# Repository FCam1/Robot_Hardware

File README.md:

# Robot_Hardware
## Descriptif fichiers :

STM32PAP board : blue pill + 2x drivers PAP  

Master board : Compatible Blue pill et STM32F103ZET6 + MAX485 +74LS241 (pour AX et XM) 

IMU adaptator : Carte a connecter sur l'IMU : [IMU280ZA-209](http://www.aceinna.com/userfiles/files/Datasheets/Inertial-System-Datasheets/6020-2810-01___IMU280ZA_Datasheet.pdf) (équipé du  connecteur CLM-110-02)

CLM-110-02 (.lib): connecteur IMU

[POLOLU 4988](https://www.pololu.com/product/1182) (.lib): driver moteur PAP  

STM32F103ZET6 (.lib): librairie EAGLE. Informations [ICI](http://wiki.stm32duino.com/index.php?title=Vcc-gnd.com_STM32F103ZET6). 

auto fuse (.lib): porte fusible (ref: [PC AUTO FUSE SOCKET](https://www.mouser.fr/ProductDetail/Keystone-Electronics/3522-2/?qs=%2fha2pyFadujcR%252bwSIP7oJU1VF30m3fPHKLRW1u8sLVY%3d))

stm32duino boards (.lib): librairie EAGLE contenant  Black Pill - Blue Pill - Maple Mini from Baite - LeafLab . Source et auteur [ICI](http://www.stm32duino.com/viewtopic.php?f=9&t=782&start=10)

## Instructions chargement bootloader :

Bluepill et stm32f103ZE: Procédure [ici](http://wiki.stm32duino.com/index.php?title=Burning_the_bootloader). Alternative pour Windows [Ici](https://github.com/rogerclarkmelbourne/Arduino_STM32/wiki/Flashing-Bootloader-for-BluePill-Boards)  

[Driver](http://www.st.com/content/st_com/en/products/development-tools/software-development-tools/stm32-software-development-tools/stm32-utilities/stsw-link009.html) pour ST-LINK/V2 sous Windows. 

Binaries : [generic_boot20_pc13.bin](https://github.com/rogerclarkmelbourne/STM32duino-bootloader/tree/master/binaries)  nécessaire pour les Bluepill et stm32f103ZE

## STM32F103ZET6 :

ST Datasheet famille STM32F1 : http://www.st.com/content/ccc/resource/technical/document/reference_manual/59/b9/ba/7f/11/af/43/d5/CD00171190.pdf/files/CD00171190.pdf/jcr:content/translations/en.CD00171190.pdf

ST Datasheet spécifique STM32F103xE : http://www.st.com/resource/en/datasheet/stm32f103ze.pdf  

### Pinouts and pin descriptions (not exhaustive):

5V tolerant : UART1, UART3, UART4, UART5, SPI2, PD8, PD9, PD10, PD11  
Not 5V tolerant : UART2, SPI3, SPI1

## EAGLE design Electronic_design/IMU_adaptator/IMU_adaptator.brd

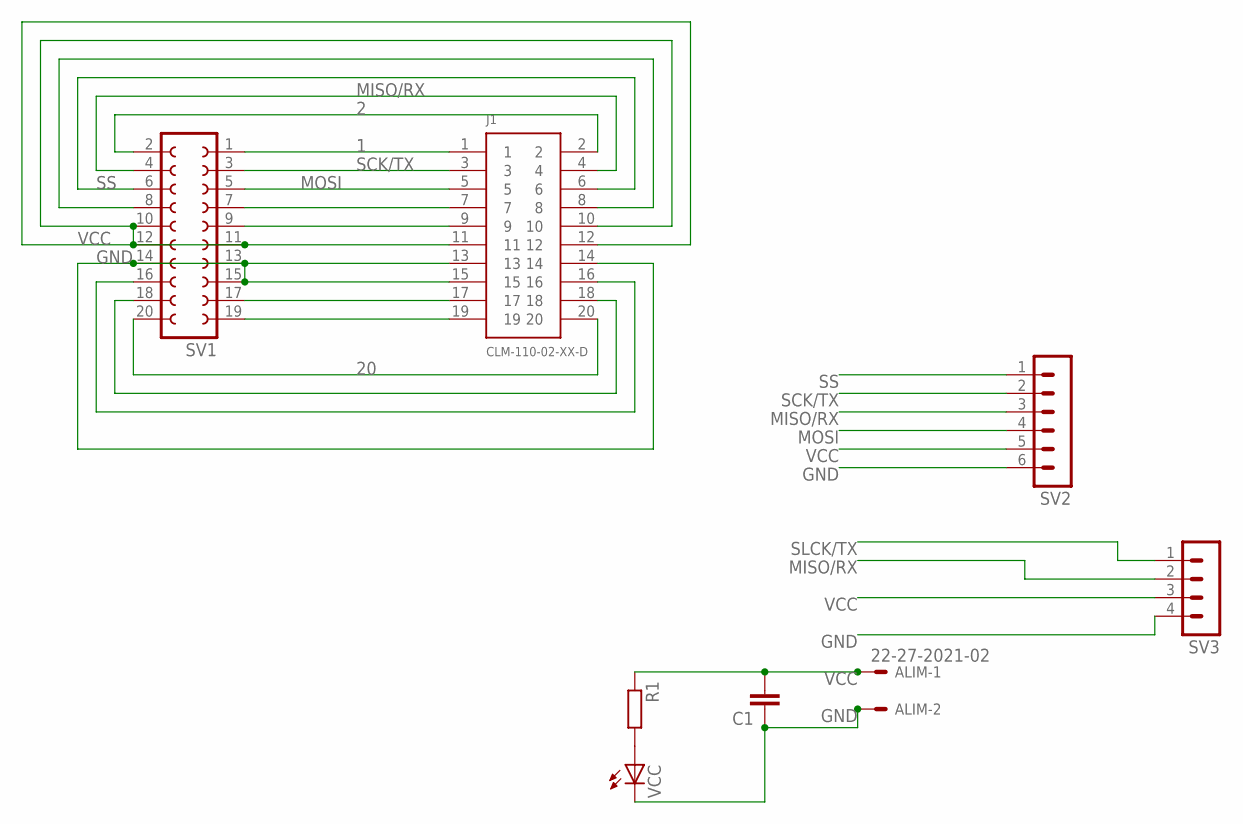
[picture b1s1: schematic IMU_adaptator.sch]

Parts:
ALIM: 22-27-2021-02; 6410-02
C1: C; C0805
J1: CLM-110-02-XX-D
R1: R-EU_0204/5; 0204/5
SV1: FE10-2
SV2: MA06-1
SV3: MA04-1
VCC: LED_ELD260; LED_LD260

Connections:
1: J1.1, SV1.1
2: J1.2, SV1.2
20: J1.20, SV1.20
GND: ALIM.2, C1.1, J1.13, J1.14, J1.15, SV1.13, SV1.14, SV1.15, SV2.6, SV3.4, VCC.K (C)
MISO/RX: J1.4, SV1.4, SV2.3, SV3.2
MOSI: J1.5, SV1.5, SV2.4
unnamed: R1.2, VCC.A
unnamed: J1.7, SV1.7
unnamed: J1.9, SV1.9
unnamed: J1.17, SV1.17
unnamed: J1.19, SV1.19
unnamed: J1.8, SV1.8
unnamed: J1.18, SV1.18
unnamed: J1.16, SV1.16
SCK/TX: J1.3, SV1.3, SV2.2
SLCK/TX: SV3.1
SS: J1.6, SV1.6, SV2.1
VCC: ALIM.1, C1.2, J1.10, J1.11, J1.12, R1.1, SV1.10, SV1.11, SV1.12, SV2.5, SV3.3

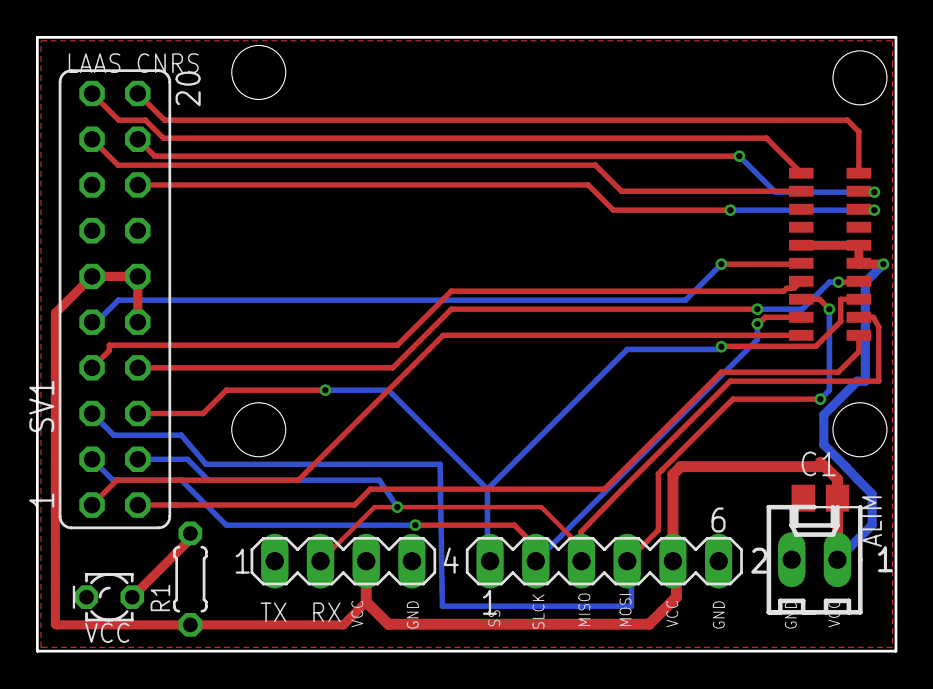
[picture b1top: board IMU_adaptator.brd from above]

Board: 2 copper layers, 47.7 x 34.1 mm, 8 parts (1 on the bottom side), 17 nets.

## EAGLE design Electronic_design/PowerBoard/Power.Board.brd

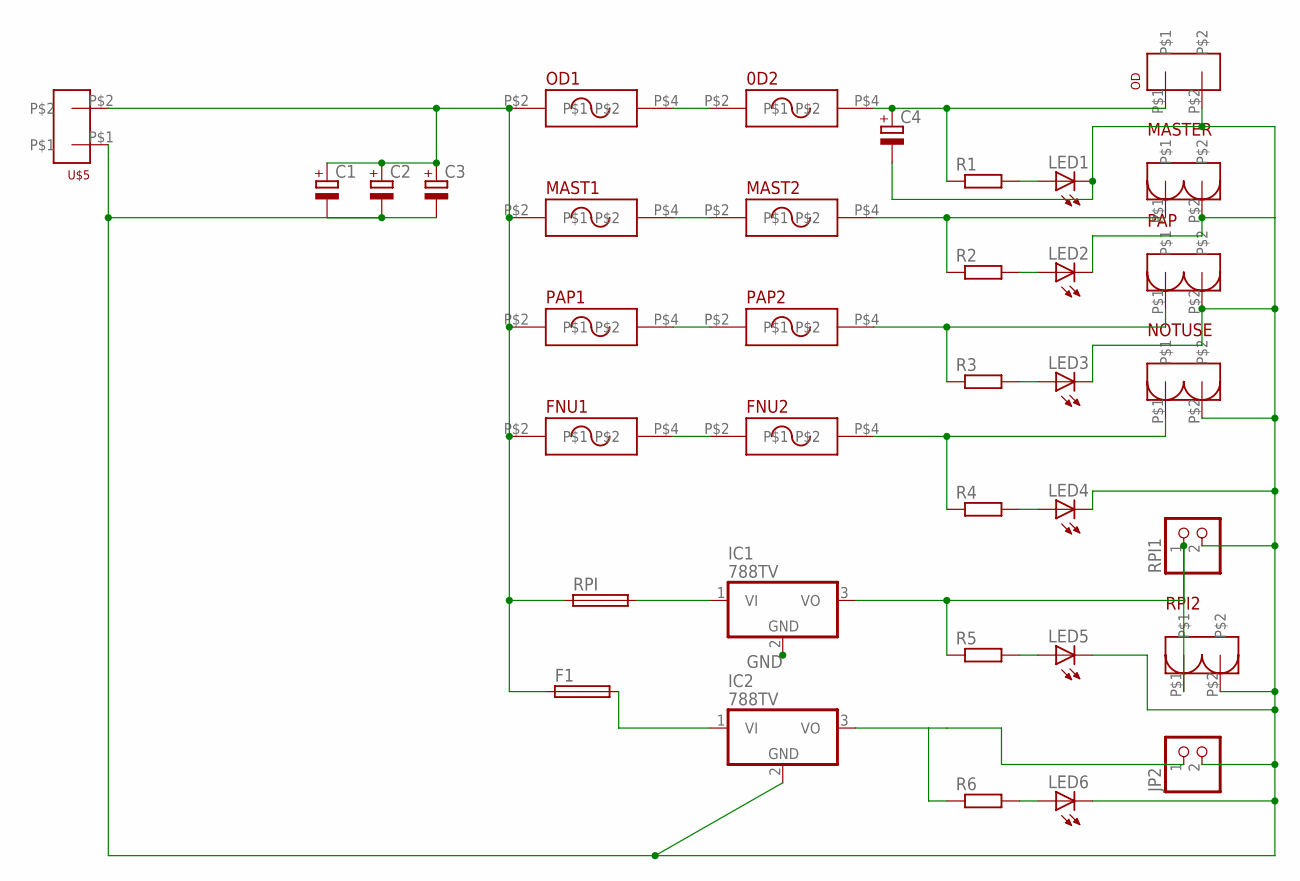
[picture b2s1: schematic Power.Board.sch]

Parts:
0D2: AUTO_FUSE
C1, C2, C3: CPOL-EUE7.5-18; E7,5-18
C4: CPOL-EUE5-13; E5-13
F1: SHK20L
FNU1, FNU2: AUTO_FUSE
IC1, IC2: 788TV; TO220V
JP2: PINHD-1X2; 1X02
LED1, LED2, LED3, LED4, LED5, LED6: LED_ELD260; LED_LD260
MAST1, MAST2: AUTO_FUSE
MASTER: GREEN_HEADER
NOTUSE: GREEN_HEADER
OD: 3MM_HEADER_2
OD1: AUTO_FUSE
PAP: GREEN_HEADER
PAP1, PAP2: AUTO_FUSE
R1, R2, R3, R4, R5, R6: R0207/10; 0207/10
RPI: SHK20L
RPI1: PINHD-1X2; 1X02
RPI2: GREEN_HEADER
U$5: 3MM_HEADER_2

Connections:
12V: C1.+, C2.+, C3.+, F1.1A, FNU1.P$2, MAST1.P$2, OD1.P$2, PAP1.P$2, RPI.1A, U$5.P$2
GND: C1.-, C2.-, C3.-, C4.-, IC1.2 (GND), IC2.2 (GND), JP2.2, LED1.K (C), LED2.K (C), LED3.K (C), LED4.K (C), LED5.K (C), LED6.K (C), MASTER.P$2, NOTUSE.P$2, OD.P$2, PAP.P$2, RPI1.2, RPI2.P$2, U$5.P$1
unnamed: PAP.P$1, PAP2.P$4, R3.1
unnamed: 0D2.P$2, OD1.P$4
unnamed: MAST1.P$4, MAST2.P$2
unnamed: PAP1.P$4, PAP2.P$2
unnamed: IC1.1 (VI), RPI.2A
unnamed: 0D2.P$4, C4.+, OD.P$1, R1.1
unnamed: MAST2.P$4, MASTER.P$1, R2.1
unnamed: IC1.3 (VO), R5.1, RPI1.1, RPI2.P$1
unnamed: IC2.3 (VO), JP2.1, R6.1
unnamed: FNU1.P$4, FNU2.P$2
unnamed: FNU2.P$4, NOTUSE.P$1, R4.1
unnamed: LED1.A, R1.2
unnamed: LED2.A, R2.2
unnamed: LED3.A, R3.2
unnamed: LED4.A, R4.2
unnamed: LED5.A, R5.2
unnamed: LED6.A, R6.2
unnamed: F1.2A, IC2.1 (VI)

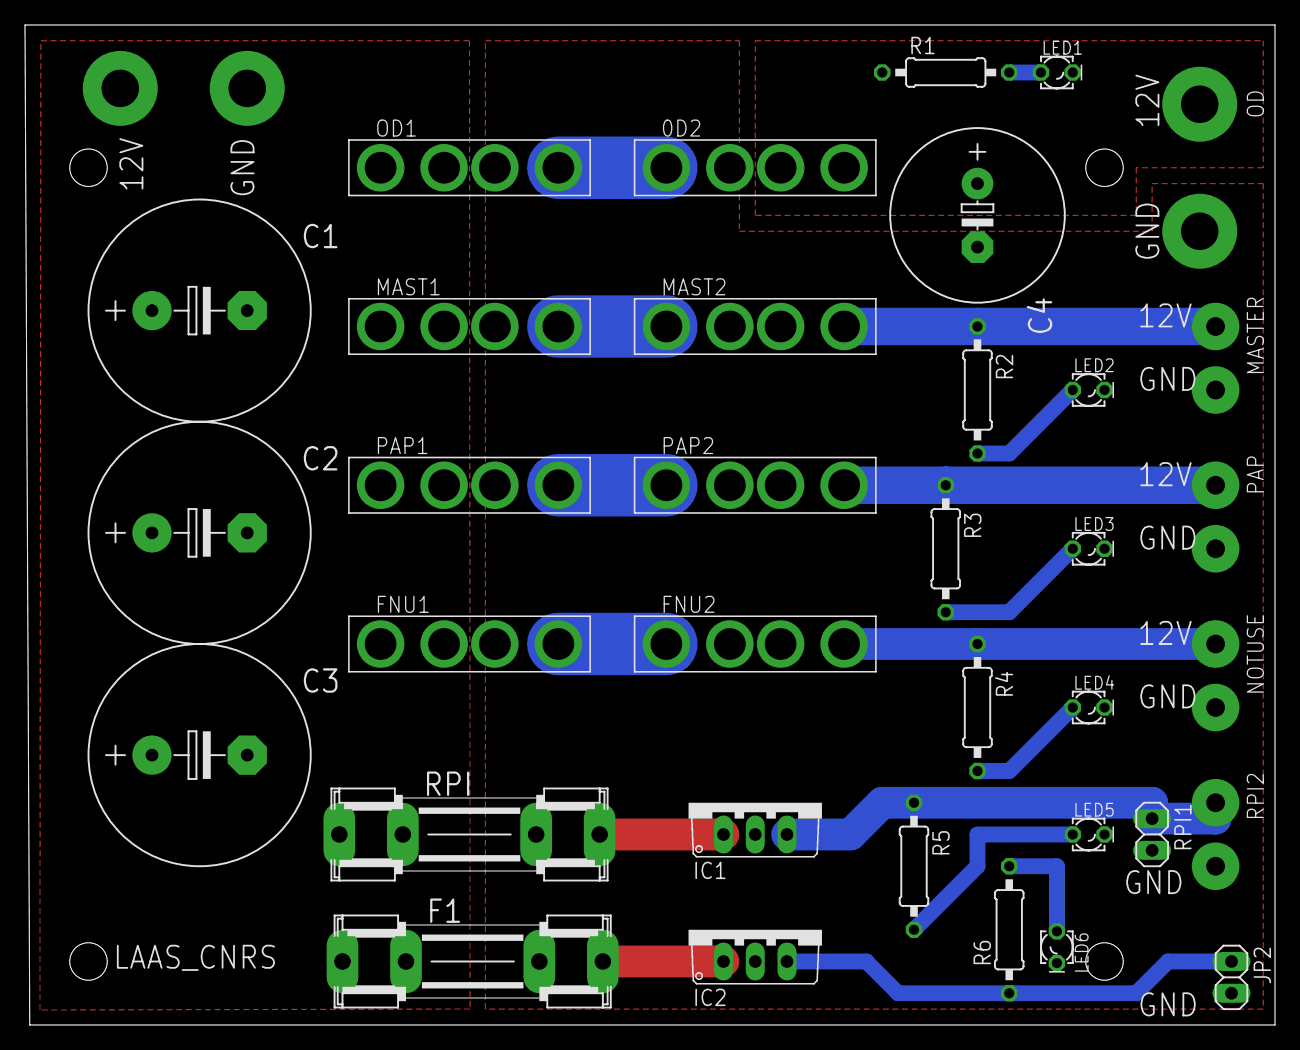
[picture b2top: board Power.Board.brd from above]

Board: 2 copper layers, 100.0 x 80.0 mm, 37 parts (0 on the bottom side), 20 nets.

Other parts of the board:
U$1: TROUS_FIXATION

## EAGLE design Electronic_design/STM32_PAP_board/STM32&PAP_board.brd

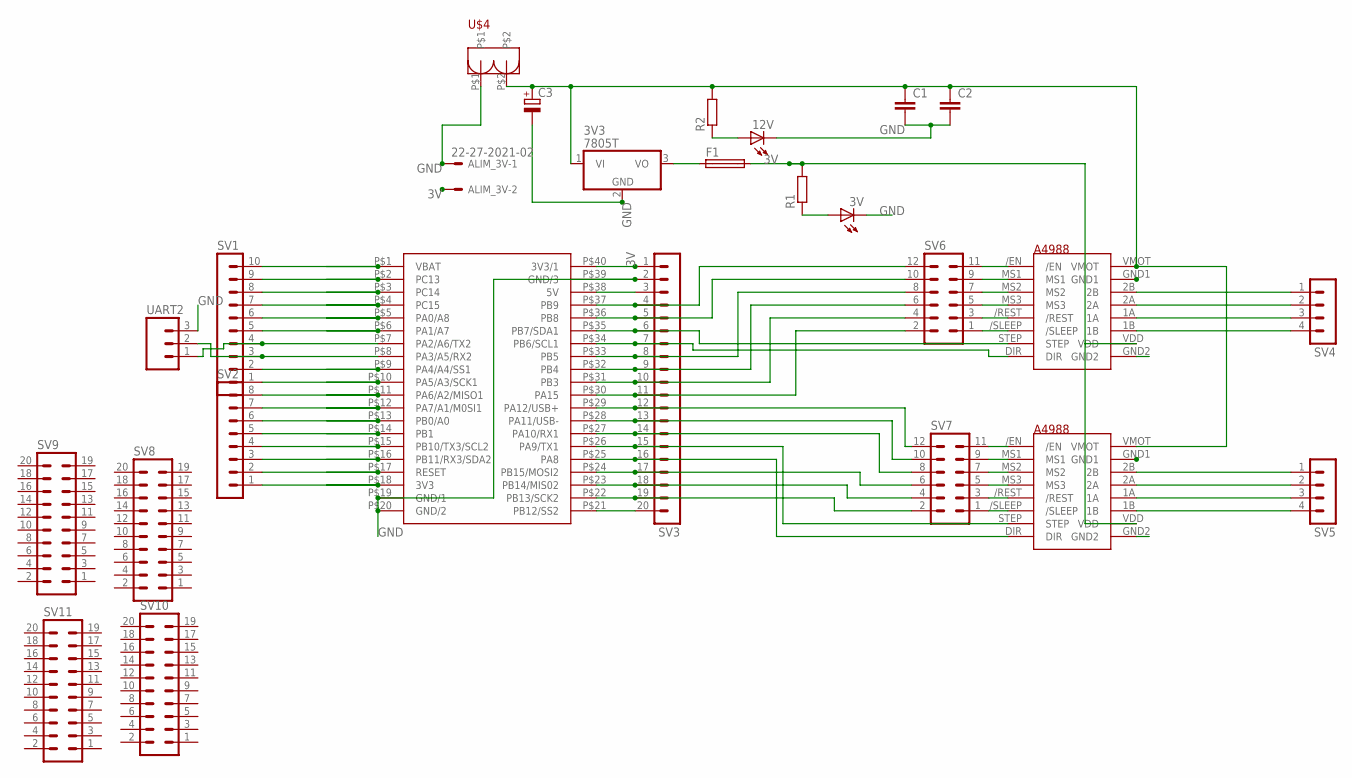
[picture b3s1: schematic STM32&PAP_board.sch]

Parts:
3V, 12V: LED_ELD260; LED_LD260
3V3: 7805T; TO220H
ALIM_3V: 22-27-2021-02; 6410-02
C1, C2: C5/5; C5B5
C3: CPOL-EUE5-13; E5-13
F1: TR5
R1, R2: R0204/7; 0204/7
SV1: MA10-1
SV2: MA08-1
SV3: MA20-1
SV4, SV5: MA04-1
SV6, SV7: MA06-2
SV8, SV9, SV10, SV11: MA10-2
U$1, U$2: POLOLU_A4988_MOTOR_DRIVER
U$3: BLUEPILL
U$4: GREEN_HEADER
UART2: MA03; 03P

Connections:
3V: ALIM_3V.2, F1.2, R1.2, SV3.1, U$1.VDD, U$2.VDD, U$3.P$40 (3V3/1)
GND: 3V.K (C), 3V3.2 (GND), 12V.K (C), ALIM_3V.1, C1.2, C2.2, C3.-, SV3.2, U$3.P$19 (GND/1), U$3.P$20 (GND/2), U$3.P$39 (GND/3), U$4.P$1, UART2.3
unnamed: SV5.1, U$2.2B
unnamed: SV5.2, U$2.2A
unnamed: SV2.1, U$3.P$18 (3V3)
unnamed: SV2.2, U$3.P$17 (RESET)
unnamed: SV2.3, U$3.P$16 (PB11/RX3/SDA2)
unnamed: SV2.4, U$3.P$15 (PB10/TX3/SCL2)
unnamed: SV2.5, U$3.P$14 (PB1)
unnamed: SV2.6, U$3.P$13 (PB0/A0)
unnamed: SV2.7, U$3.P$12 (PA7/A1/M0SI1)
unnamed: SV2.8, U$3.P$11 (PA6/A2/MISO1)
unnamed: SV1.1, U$3.P$10 (PA5/A3/SCK1)
unnamed: SV1.2, U$3.P$9 (PA4/A4/SS1)
unnamed: SV1.3, U$3.P$8 (PA3/A5/RX2), UART2.2
unnamed: SV1.4, U$3.P$7 (PA2/A6/TX2), UART2.1
unnamed: SV1.5, U$3.P$6 (PA1/A7)
unnamed: SV1.6, U$3.P$5 (PA0/A8)
unnamed: SV1.7, U$3.P$4 (PC15)
unnamed: SV1.8, U$3.P$3 (PC14)
unnamed: SV1.9, U$3.P$2 (PC13)
unnamed: SV1.10, U$3.P$1 (VBAT)
unnamed: SV6.1, U$1./SLEEP
unnamed: SV5.3, U$2.1A
unnamed: SV3.3, U$3.P$38 (5V)
unnamed: SV3.4, SV6.12, U$3.P$37 (PB9)
unnamed: SV3.5, SV6.10, U$3.P$36 (PB8)
unnamed: SV3.7, U$1.DIR, U$3.P$34 (PB6/SCL1)
unnamed: SV3.9, SV6.6, U$3.P$32 (PB4)
unnamed: SV3.10, SV6.4, U$3.P$31 (PB3)
unnamed: SV3.11, SV6.2, U$3.P$30 (PA15)
unnamed: SV3.12, SV7.12, U$3.P$29 (PA12/USB+)
unnamed: SV3.13, SV7.10, U$3.P$28 (PA11/USB-)
unnamed: SV3.14, SV7.8, U$3.P$27 (PA10/RX1)
unnamed: SV3.15, U$2.STEP, U$3.P$26 (PA9/TX1)
unnamed: SV3.16, U$2.DIR, U$3.P$25 (PA8)
unnamed: SV3.17, SV7.6, U$3.P$24 (PB15/MOSI2)
unnamed: SV3.18, SV7.4, U$3.P$23 (PB14/MIS02)
unnamed: SV3.19, SV7.2, U$3.P$22 (PB13/SCK2)
unnamed: SV3.20, U$3.P$21 (PB12/SS2)
unnamed: 3V3.3 (VO), F1.1
unnamed: 3V3.1 (VI), C1.1, C2.1, C3.+, R2.2, U$1.VMOT, U$2.VMOT, U$4.P$2
unnamed: 3V.A, R1.1
unnamed: SV5.4, U$2.1B
unnamed: 12V.A, R2.1
unnamed: SV4.1, U$1.2B
unnamed: SV4.2, U$1.2A
unnamed: SV4.3, U$1.1A
unnamed: SV4.4, U$1.1B
unnamed: SV6.3, U$1./REST
unnamed: SV6.5, U$1.MS3
unnamed: SV6.7, U$1.MS2
unnamed: SV6.9, U$1.MS1
unnamed: SV6.11, U$1./EN
unnamed: SV3.6, U$1.STEP, U$3.P$35 (PB7/SDA1)
unnamed: SV3.8, SV6.8, U$3.P$33 (PB5)
unnamed: SV7.11, U$2./EN
unnamed: SV7.9, U$2.MS1
unnamed: SV7.7, U$2.MS2
unnamed: SV7.5, U$2.MS3
unnamed: SV7.3, U$2./REST
unnamed: SV7.1, U$2./SLEEP

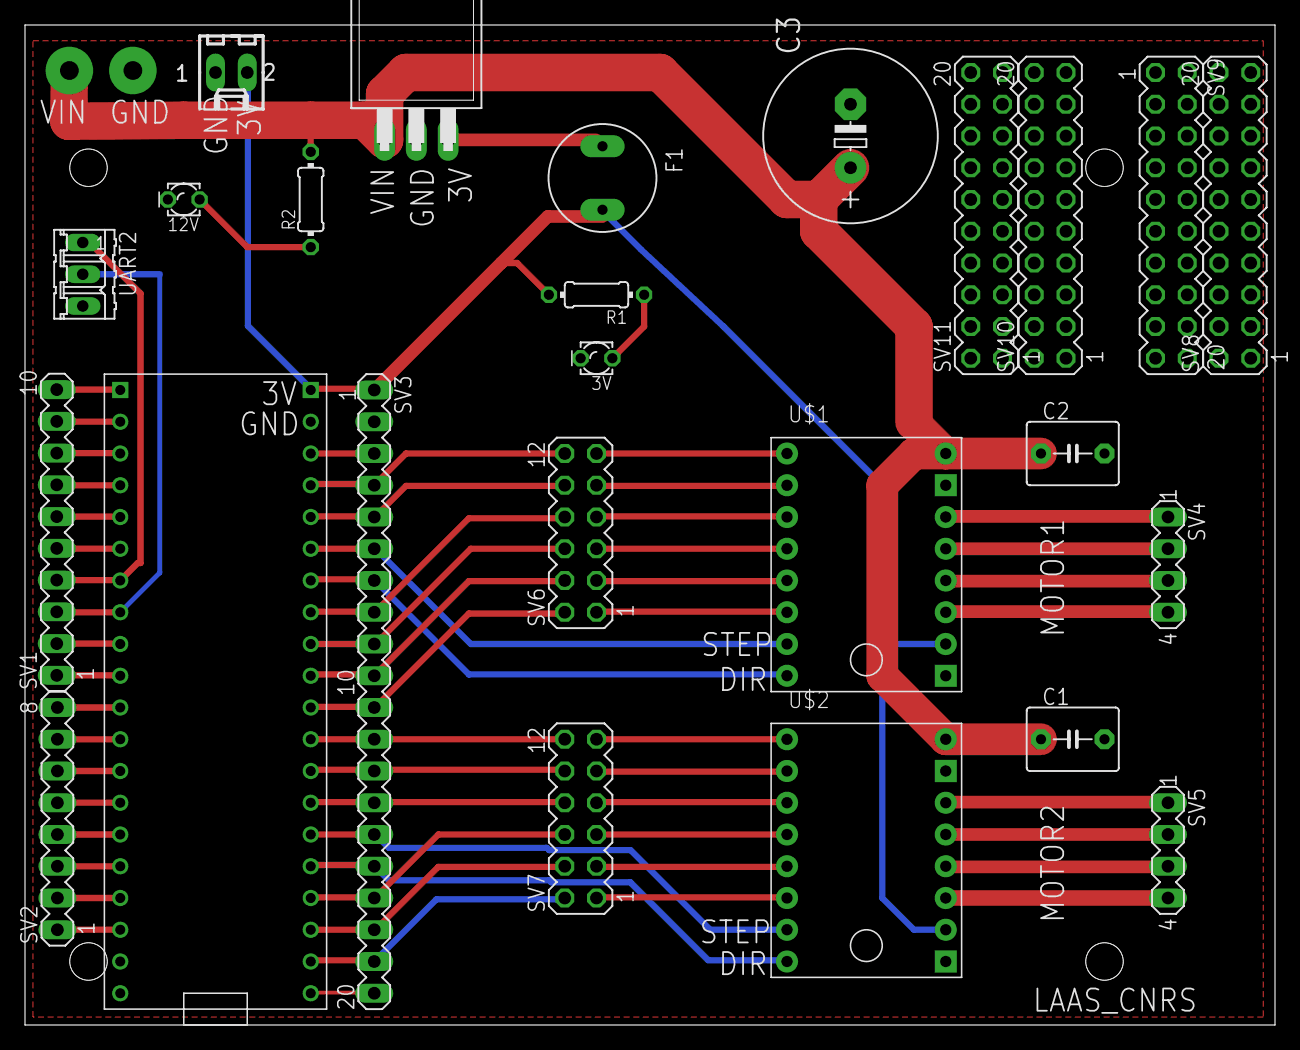
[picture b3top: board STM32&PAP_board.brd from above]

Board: 2 copper layers, 100.0 x 80.0 mm, 27 parts (0 on the bottom side), 62 nets.

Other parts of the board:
U$5: TROUS_FIXATION

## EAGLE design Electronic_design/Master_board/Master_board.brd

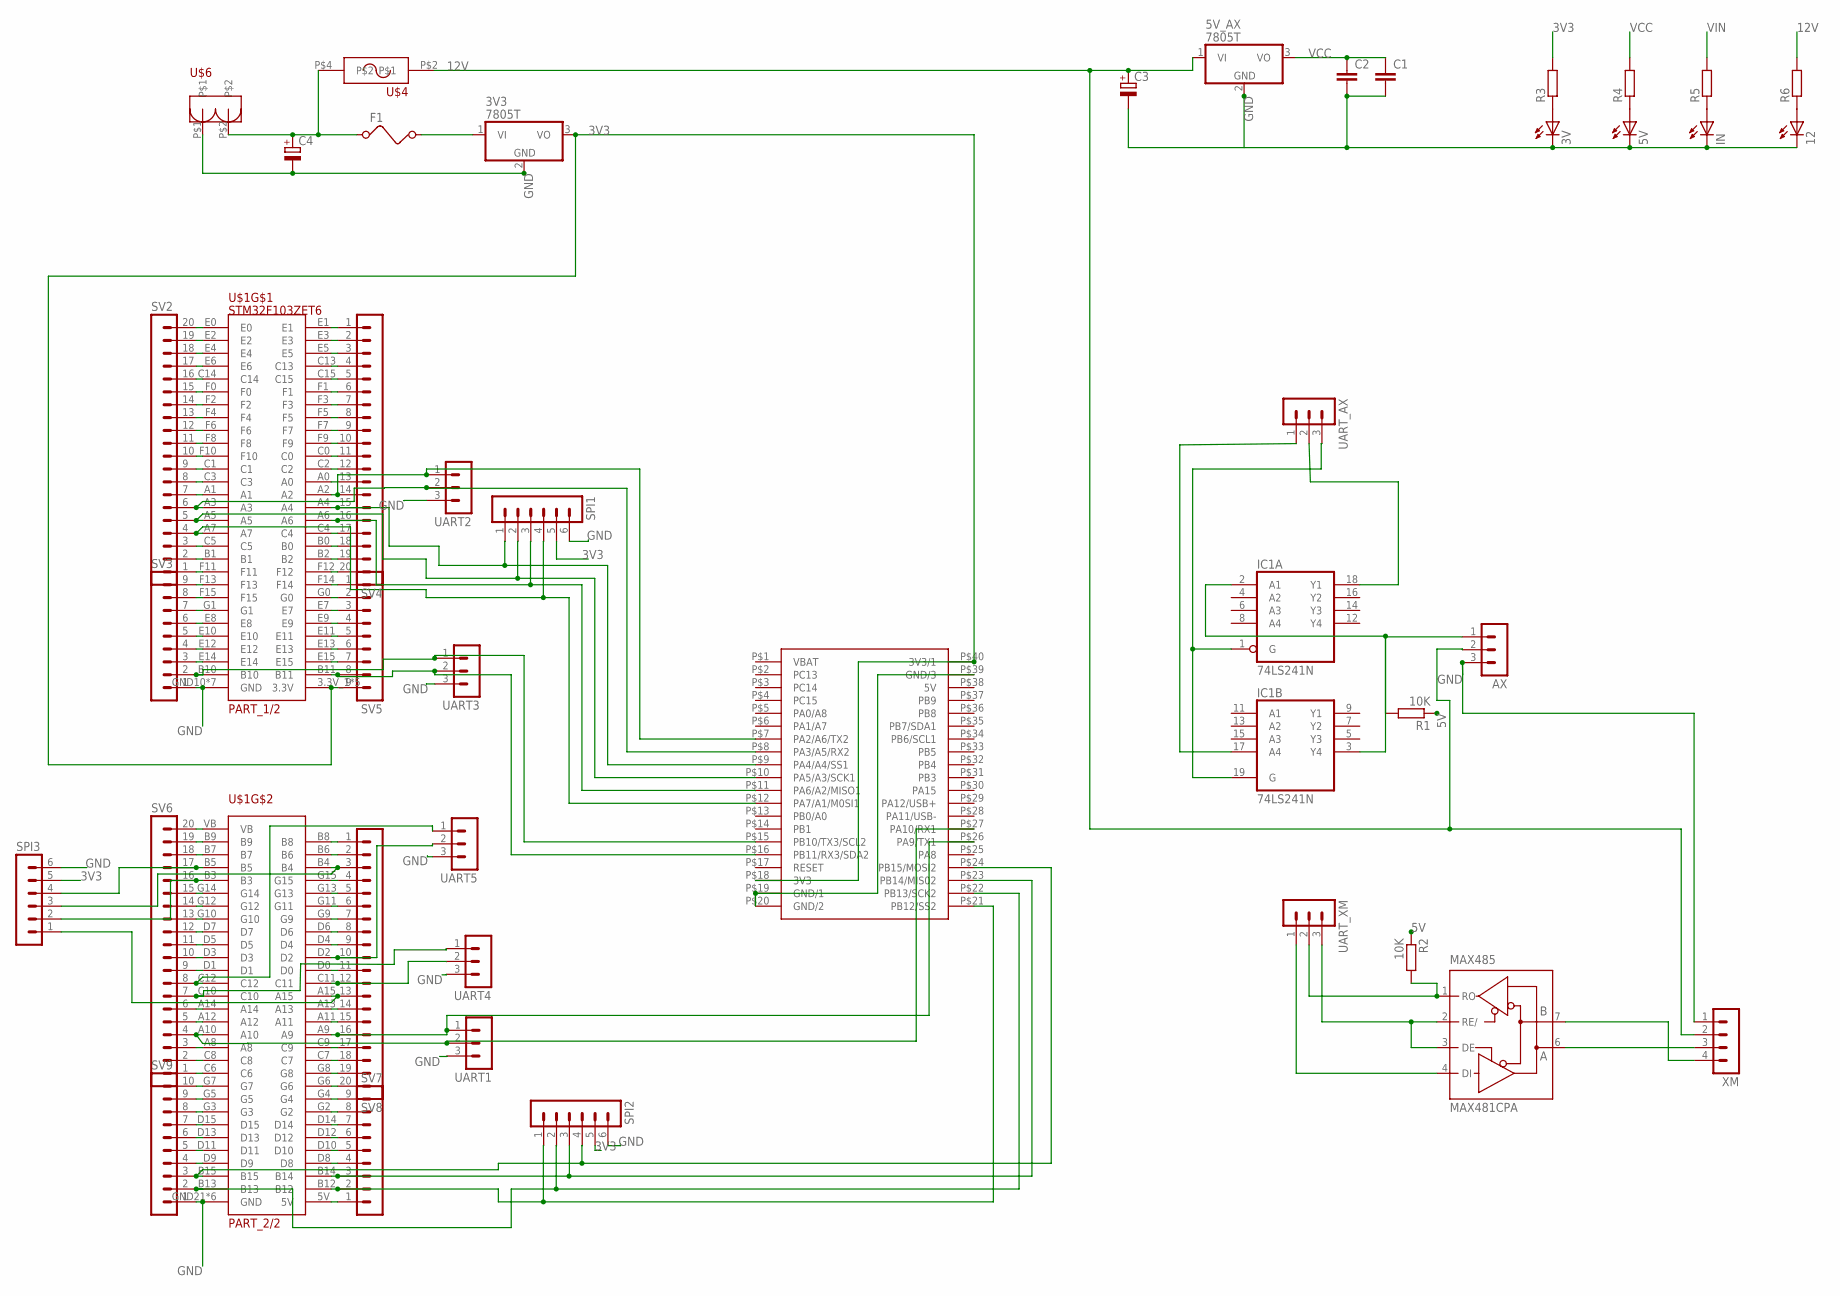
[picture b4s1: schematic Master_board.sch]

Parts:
3V, 5V, 12: LED_ELD260; LED_LD260
3V3, 5V_AX: 7805T; TO220H
AX: MA03-1
C1, C2: C-EU025-024X044; C025-024X044
C3, C4: CPOL-EUE5-10.5; E5-10,5
F1: FUSE
IC1: 74LS241N; DIL20
IN: LED_ELD260; LED_LD260
MAX485: MAX481CPA; DIL08
R1, R2: 10K; 0309/12
R3, R4, R5, R6: R-EU_0204/5; 0204/5
SPI1, SPI2, SPI3: MA06-1
SV2, SV4, SV6, SV8: MA20-1L
SV3, SV5, SV7: MA09-1
SV9: MA10-1
U$1: M32F103ZET6_DEV_BOARD; STM32F103ZET6_DEV_BOARD
U$2: BLUEPILL
U$4: AUTO_FUSE
U$6: GREEN_HEADER
UART1, UART2, UART3, UART4, UART5: MA03-1
UART_AX: MA03-1
UART_XM: MA03-1
XM: MA04-1

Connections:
3V3: 3V3.3 (VO), R3.2, SPI1.5, SPI2.5, SPI3.5, SV5.9, U$1.3.3V_1 (3.3V), U$1.3.3V_2 (3.3V), U$1.3.3V_3 (3.3V), U$1.3.3V_4 (3.3V), U$1.3.3V_5 (3.3V), U$2.P$18 (3V3), U$2.P$40 (3V3/1)
5V: R1.1, R2.1
12V: 5V_AX.1 (VI), AX.2, C3.+, R6.2, U$4.P$2, XM.2
CTRL_AX: IC1.1 (G), IC1.19 (G), UART_AX.3
CTRL_XM: MAX485.2 (RE/), MAX485.3 (DE), UART_XM.3
D+: MAX485.6 (A), XM.3
D-: MAX485.7 (B), XM.4
DATA_AX: AX.1, IC1.2 (A1), IC1.3 (Y4), R1.2
GND: 3V.K (C), 3V3.2 (GND), 5V.K (C), 5V_AX.2 (GND), 12.K (C), AX.3, C1.2, C2.2, C3.-, C4.-, IC1.10 (GND), IN.K (C), MAX485.5 (GND), SPI1.6, SPI2.6, SPI3.6, SV3.1, SV9.1, U$1.GND10 (GND), U$1.GND11 (GND), U$1.GND12 (GND), U$1.GND13 (GND), U$1.GND14 (GND), U$1.GND15 (GND), U$1.GND16 (GND), U$1.GND21 (GND), U$1.GND22 (GND), U$1.GND24 (GND), U$1.GND25 (GND), U$1.GND26 (GND), U$1.GND_20 (GND), U$2.P$19 (GND/1), U$2.P$20 (GND/2), U$2.P$39 (GND/3), U$6.P$1, UART1.3, UART2.3, UART3.3, UART4.3, UART5.3, XM.1
MISO1: SPI1.3, SV4.16, U$1.A6, U$2.P$11 (PA6/A2/MISO1)
MISO2: SPI2.3, SV7.3, U$1.B14, U$2.P$23 (PB14/MIS02)
MISO3: SPI3.3, SV8.3, U$1.B4
MOSI1: SPI1.4, SV2.4, U$1.A7, U$2.P$12 (PA7/A1/M0SI1)
MOSI2: SPI2.4, SV9.3, U$1.B15, U$2.P$24 (PB15/MOSI2)
MOSI3: SPI3.4, SV6.17, U$1.B5
unnamed: 3V.A, R3.1
unnamed: 5V.A, R4.1
unnamed: IN.A, R5.1
unnamed: 12.A, R6.1
unnamed: SV2.1, U$1.F11
unnamed: SV2.2, U$1.B1
unnamed: SV2.3, U$1.C5
unnamed: SV2.7, U$1.A1
unnamed: SV2.8, U$1.C3
unnamed: SV2.9, U$1.C1
unnamed: SV2.10, U$1.F10
unnamed: SV2.11, U$1.F8
unnamed: SV2.12, U$1.F6
unnamed: SV2.13, U$1.F4
unnamed: SV2.14, U$1.F2
unnamed: SV2.15, U$1.F0
unnamed: SV2.16, U$1.C14
unnamed: SV2.17, U$1.E6
unnamed: SV2.18, U$1.E4
unnamed: SV2.19, U$1.E2
unnamed: SV2.20, U$1.E0
unnamed: SV3.3, U$1.E14
unnamed: SV3.4, U$1.E12
unnamed: SV3.5, U$1.E10
unnamed: SV3.6, U$1.E8
unnamed: SV3.7, U$1.G1
unnamed: SV3.8, U$1.F15
unnamed: SV3.9, U$1.F13
unnamed: SV4.1, U$1.E1
unnamed: SV4.2, U$1.E3
unnamed: SV4.3, U$1.E5
unnamed: SV4.4, U$1.C13
unnamed: SV4.5, U$1.C15
unnamed: SV4.6, U$1.F1
unnamed: SV4.7, U$1.F3
unnamed: SV4.8, U$1.F5
unnamed: SV4.9, U$1.F7
unnamed: SV4.10, U$1.F9
unnamed: SV4.11, U$1.C0
unnamed: SV4.12, U$1.C2
unnamed: SV4.13, U$1.A0
unnamed: SV4.17, U$1.C4
unnamed: SV4.18, U$1.B0
unnamed: SV4.19, U$1.B2
unnamed: SV4.20, U$1.F12
unnamed: SV5.1, U$1.F14
unnamed: SV5.2, U$1.G0
unnamed: SV5.3, U$1.E7
unnamed: SV5.4, U$1.E9
unnamed: SV5.5, U$1.E11
unnamed: SV5.6, U$1.E13
unnamed: SV5.7, U$1.E15
unnamed: SV6.1, U$1.C6
unnamed: SV6.2, U$1.C8
unnamed: SV6.3, U$1.A8
unnamed: SV6.5, U$1.A12
unnamed: SV6.6, U$1.A14
unnamed: SV6.9, U$1.D1
unnamed: SV6.10, U$1.D3
unnamed: SV6.11, U$1.D5
unnamed: SV6.12, U$1.D7
unnamed: SV6.13, U$1.G10
unnamed: SV6.14, U$1.G12
unnamed: SV6.15, U$1.G14
unnamed: SV6.18, U$1.B7
unnamed: SV6.19, U$1.B9
unnamed: SV6.20, U$1.VB
unnamed: SV7.1, U$1.5V
unnamed: SV7.4, U$1.D8
unnamed: SV7.5, U$1.D10
unnamed: SV7.6, U$1.D12
unnamed: SV7.7, U$1.D14
unnamed: SV7.8, U$1.G2
unnamed: SV7.9, U$1.G4
unnamed: SV8.1, U$1.B8
unnamed: SV8.2, U$1.B6
unnamed: SV8.4, U$1.G15
unnamed: SV8.5, U$1.G13
unnamed: SV8.6, U$1.G11
unnamed: SV8.7, U$1.G9
unnamed: SV8.8, U$1.D6
unnamed: SV8.9, U$1.D4
unnamed: SV8.11, U$1.D0
unnamed: SV8.14, U$1.A13
unnamed: SV8.15, U$1.A11
unnamed: SV8.17, U$1.C9
unnamed: SV8.18, U$1.C7
unnamed: SV8.19, U$1.G8
unnamed: SV8.20, U$1.G6
unnamed: SV9.4, U$1.D9
unnamed: SV9.5, U$1.D11
unnamed: SV9.6, U$1.D13
unnamed: SV9.7, U$1.D15
unnamed: SV9.8, U$1.G3
unnamed: SV9.9, U$1.G5
unnamed: SV9.10, U$1.G7
unnamed: 3V3.1 (VI), F1.2
NSS1: SPI1.1, SV4.15, U$1.A4, U$2.P$9 (PA4/A4/SS1)
NSS2: SPI2.1, SV7.2, U$1.B12, U$2.P$21 (PB12/SS2)
NSS3: SPI3.1, SV8.13, U$1.A15
RX1: SV6.4, U$1.A10, U$2.P$27 (PA10/RX1), UART1.2
RX2: SV2.6, U$1.A3, U$2.P$8 (PA3/A5/RX2), UART2.2
RX3: SV5.8, U$1.B11, U$2.P$16 (PB11/RX3/SDA2), UART3.2
RX4: SV8.12, U$1.C11, UART4.2
RX5: SV8.10, U$1.D2, UART5.2
RX_AX: IC1.18 (Y1), UART_AX.2
RX_XM: MAX485.1 (RO), R2.2, UART_XM.2
SCK1: SPI1.2, SV2.5, U$1.A5, U$2.P$10 (PA5/A3/SCK1)
SCK2: SPI2.2, SV9.2, U$1.B13, U$2.P$22 (PB13/SCK2)
SCK3: SPI3.2, SV6.16, U$1.B3
TX1: SV8.16, U$1.A9, U$2.P$26 (PA9/TX1), UART1.1
TX2: SV4.14, U$1.A2, U$2.P$7 (PA2/A6/TX2), UART2.1
TX3: SV3.2, U$1.B10, U$2.P$15 (PB10/TX3/SCL2), UART3.1
TX4: SV6.7, U$1.C10, UART4.1
TX5: SV6.8, U$1.C12, UART5.1
TX_AX: IC1.17 (A4), UART_AX.1
TX_XM: MAX485.4 (DI), UART_XM.1
VCC: 5V_AX.3 (VO), C1.1, C2.1, IC1.20 (VCC), MAX485.8 (VCC), R4.2
VIN: C4.+, F1.1, R5.2, U$4.P$4, U$6.P$2

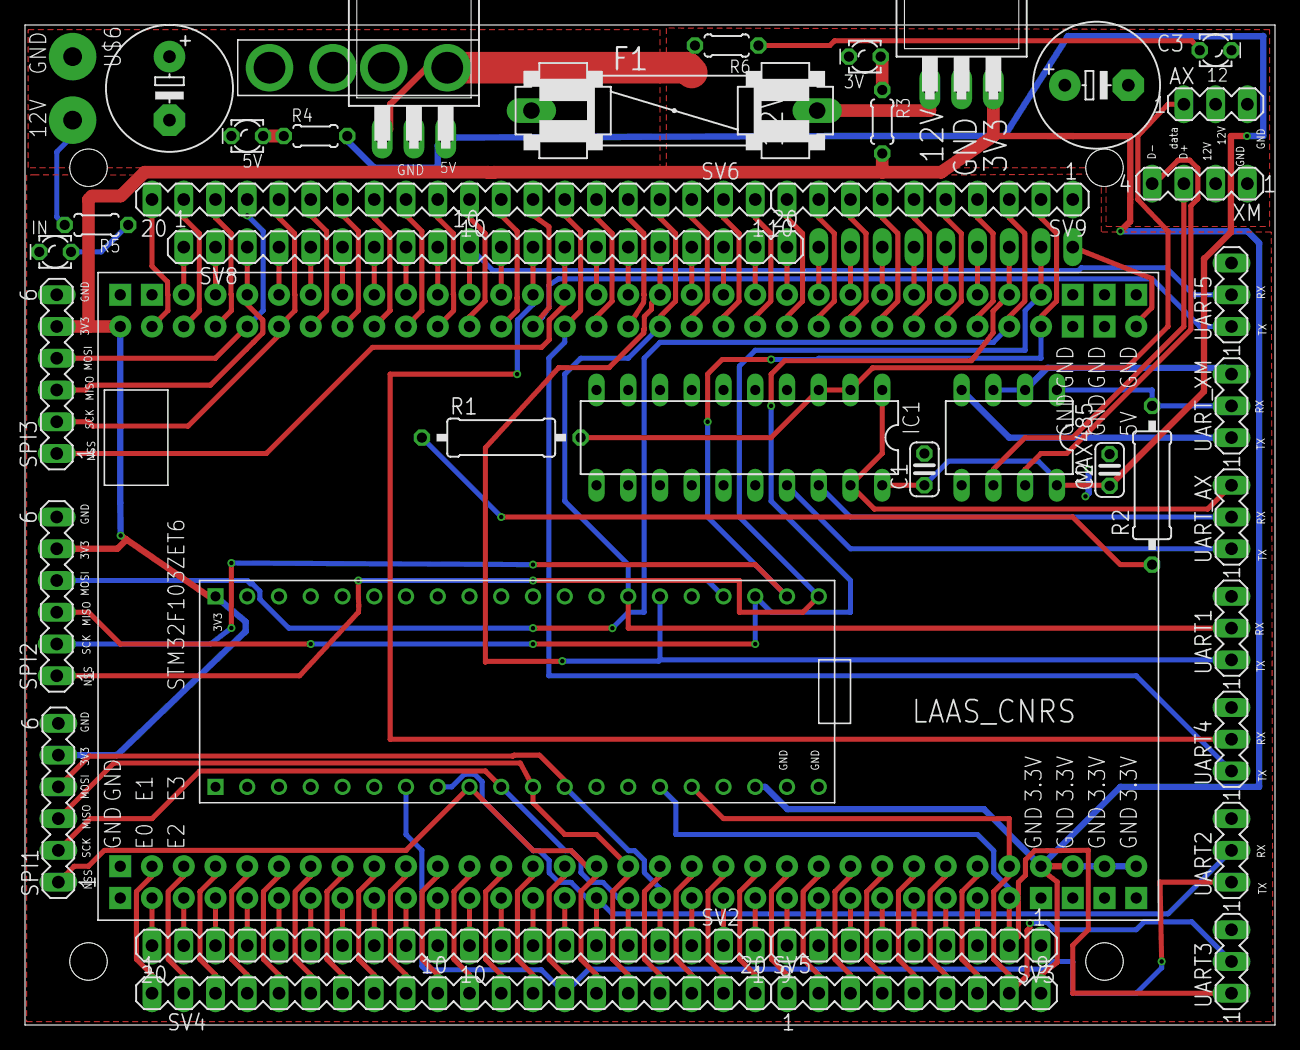
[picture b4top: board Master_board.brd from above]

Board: 2 copper layers, 100.0 x 80.0 mm, 44 parts (1 on the bottom side), 134 nets.

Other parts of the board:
U$5: TROUS_FIXATION

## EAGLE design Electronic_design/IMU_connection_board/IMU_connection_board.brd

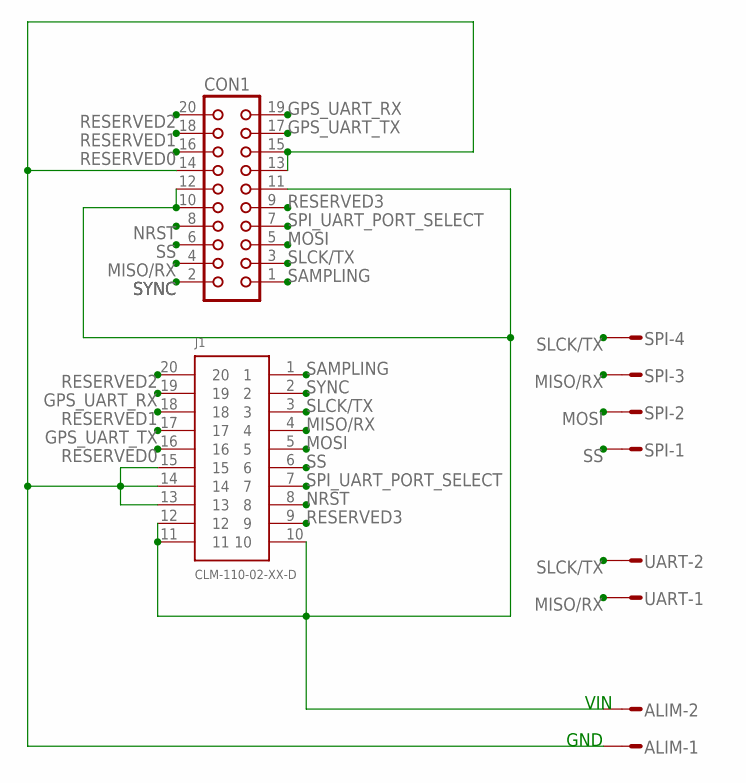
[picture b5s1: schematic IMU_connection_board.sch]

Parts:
ALIM: L02P
CON1: CON20
J1: CLM-110-02-XX-D
SPI: L04P
UART: L02P

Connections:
GND: ALIM.1, CON1.13, CON1.14, CON1.15, J1.13, J1.14, J1.15
GPS_UART_RX: CON1.19, J1.19
GPS_UART_TX: CON1.17, J1.17
MISO/RX: CON1.4, J1.4, SPI.3, UART.1
MOSI: CON1.5, J1.5, SPI.2
NRST: CON1.8, J1.8
RESERVED0: CON1.16, J1.16
RESERVED1: CON1.18, J1.18
RESERVED2: CON1.20, J1.20
RESERVED3: CON1.9, J1.9
SAMPLING: CON1.1, J1.1
SLCK/TX: CON1.3, J1.3, SPI.4, UART.2
SPI_UART_PORT_SELECT: CON1.7, J1.7
SS: CON1.6, J1.6, SPI.1
SYNC: CON1.2, J1.2
VIN: ALIM.2, CON1.10, CON1.11, CON1.12, J1.10, J1.11, J1.12

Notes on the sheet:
GND
VIN

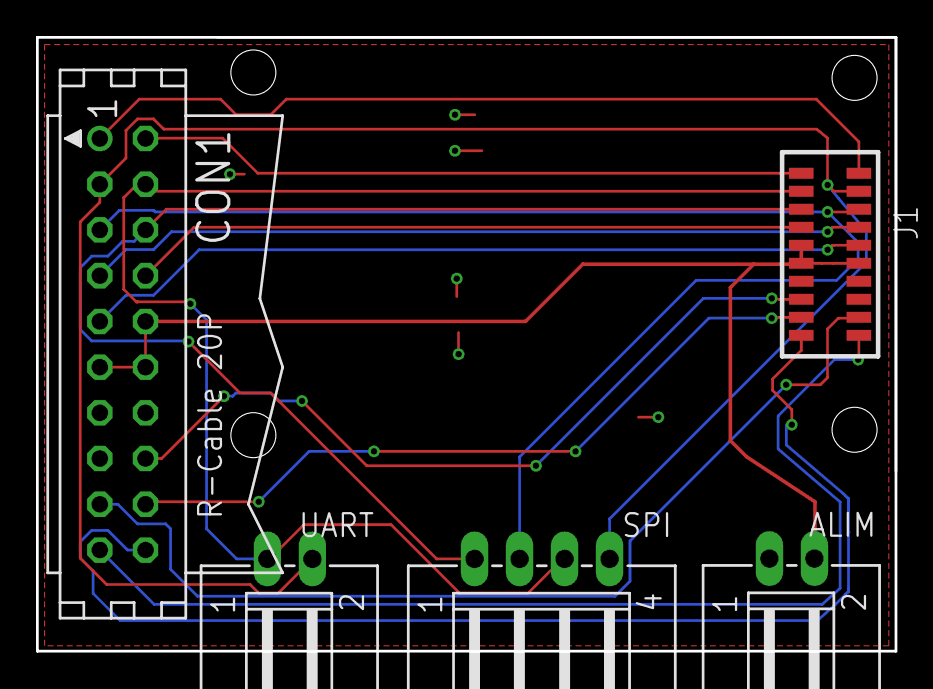
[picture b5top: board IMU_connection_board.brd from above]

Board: 2 copper layers, 47.7 x 34.1 mm, 5 parts (0 on the bottom side), 16 nets.

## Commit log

2018-01-05 reroutage carte IMU et STEPPER
2018-01-08 suppression versionnage eagle
2018-01-08 modif POLOLU et STM32F103
2018-01-08 MAJ POLOLU
2018-01-09 correction erreurs
2018-01-09 add stm32 lib
2018-01-09 modification regulateur 3V3
2018-01-09 routage
2018-01-09 suppression carte half duplex
2018-01-09 DRC check OK
2018-01-10 add NAME
2018-01-10 DEL version
2018-01-10 modification repertoire
2018-01-10 ajout connecteur vert et trous de fixation
2018-01-10 ameliorations
2018-01-11 ajout alim aux connect SPI et UART
2018-01-11 elargissement pistes
2018-01-11 modif plan de masse
2018-01-11 suppression fichiers
2018-01-11 suppression connecteur inutile
2018-01-11 ajout condensateurs
2018-01-11 modif layers
2018-01-11 CRC OK
2018-01-11 modif piste
2018-01-12 ajout leds alim
2018-01-12 ajout LED
2018-01-12 modif sens connecteurs puissance
2018-02-06 nouveau routage
2018-02-12 add STM32F103ZET6 comments
2018-03-14 ajout images schematic
2018-03-30 ajout photos
